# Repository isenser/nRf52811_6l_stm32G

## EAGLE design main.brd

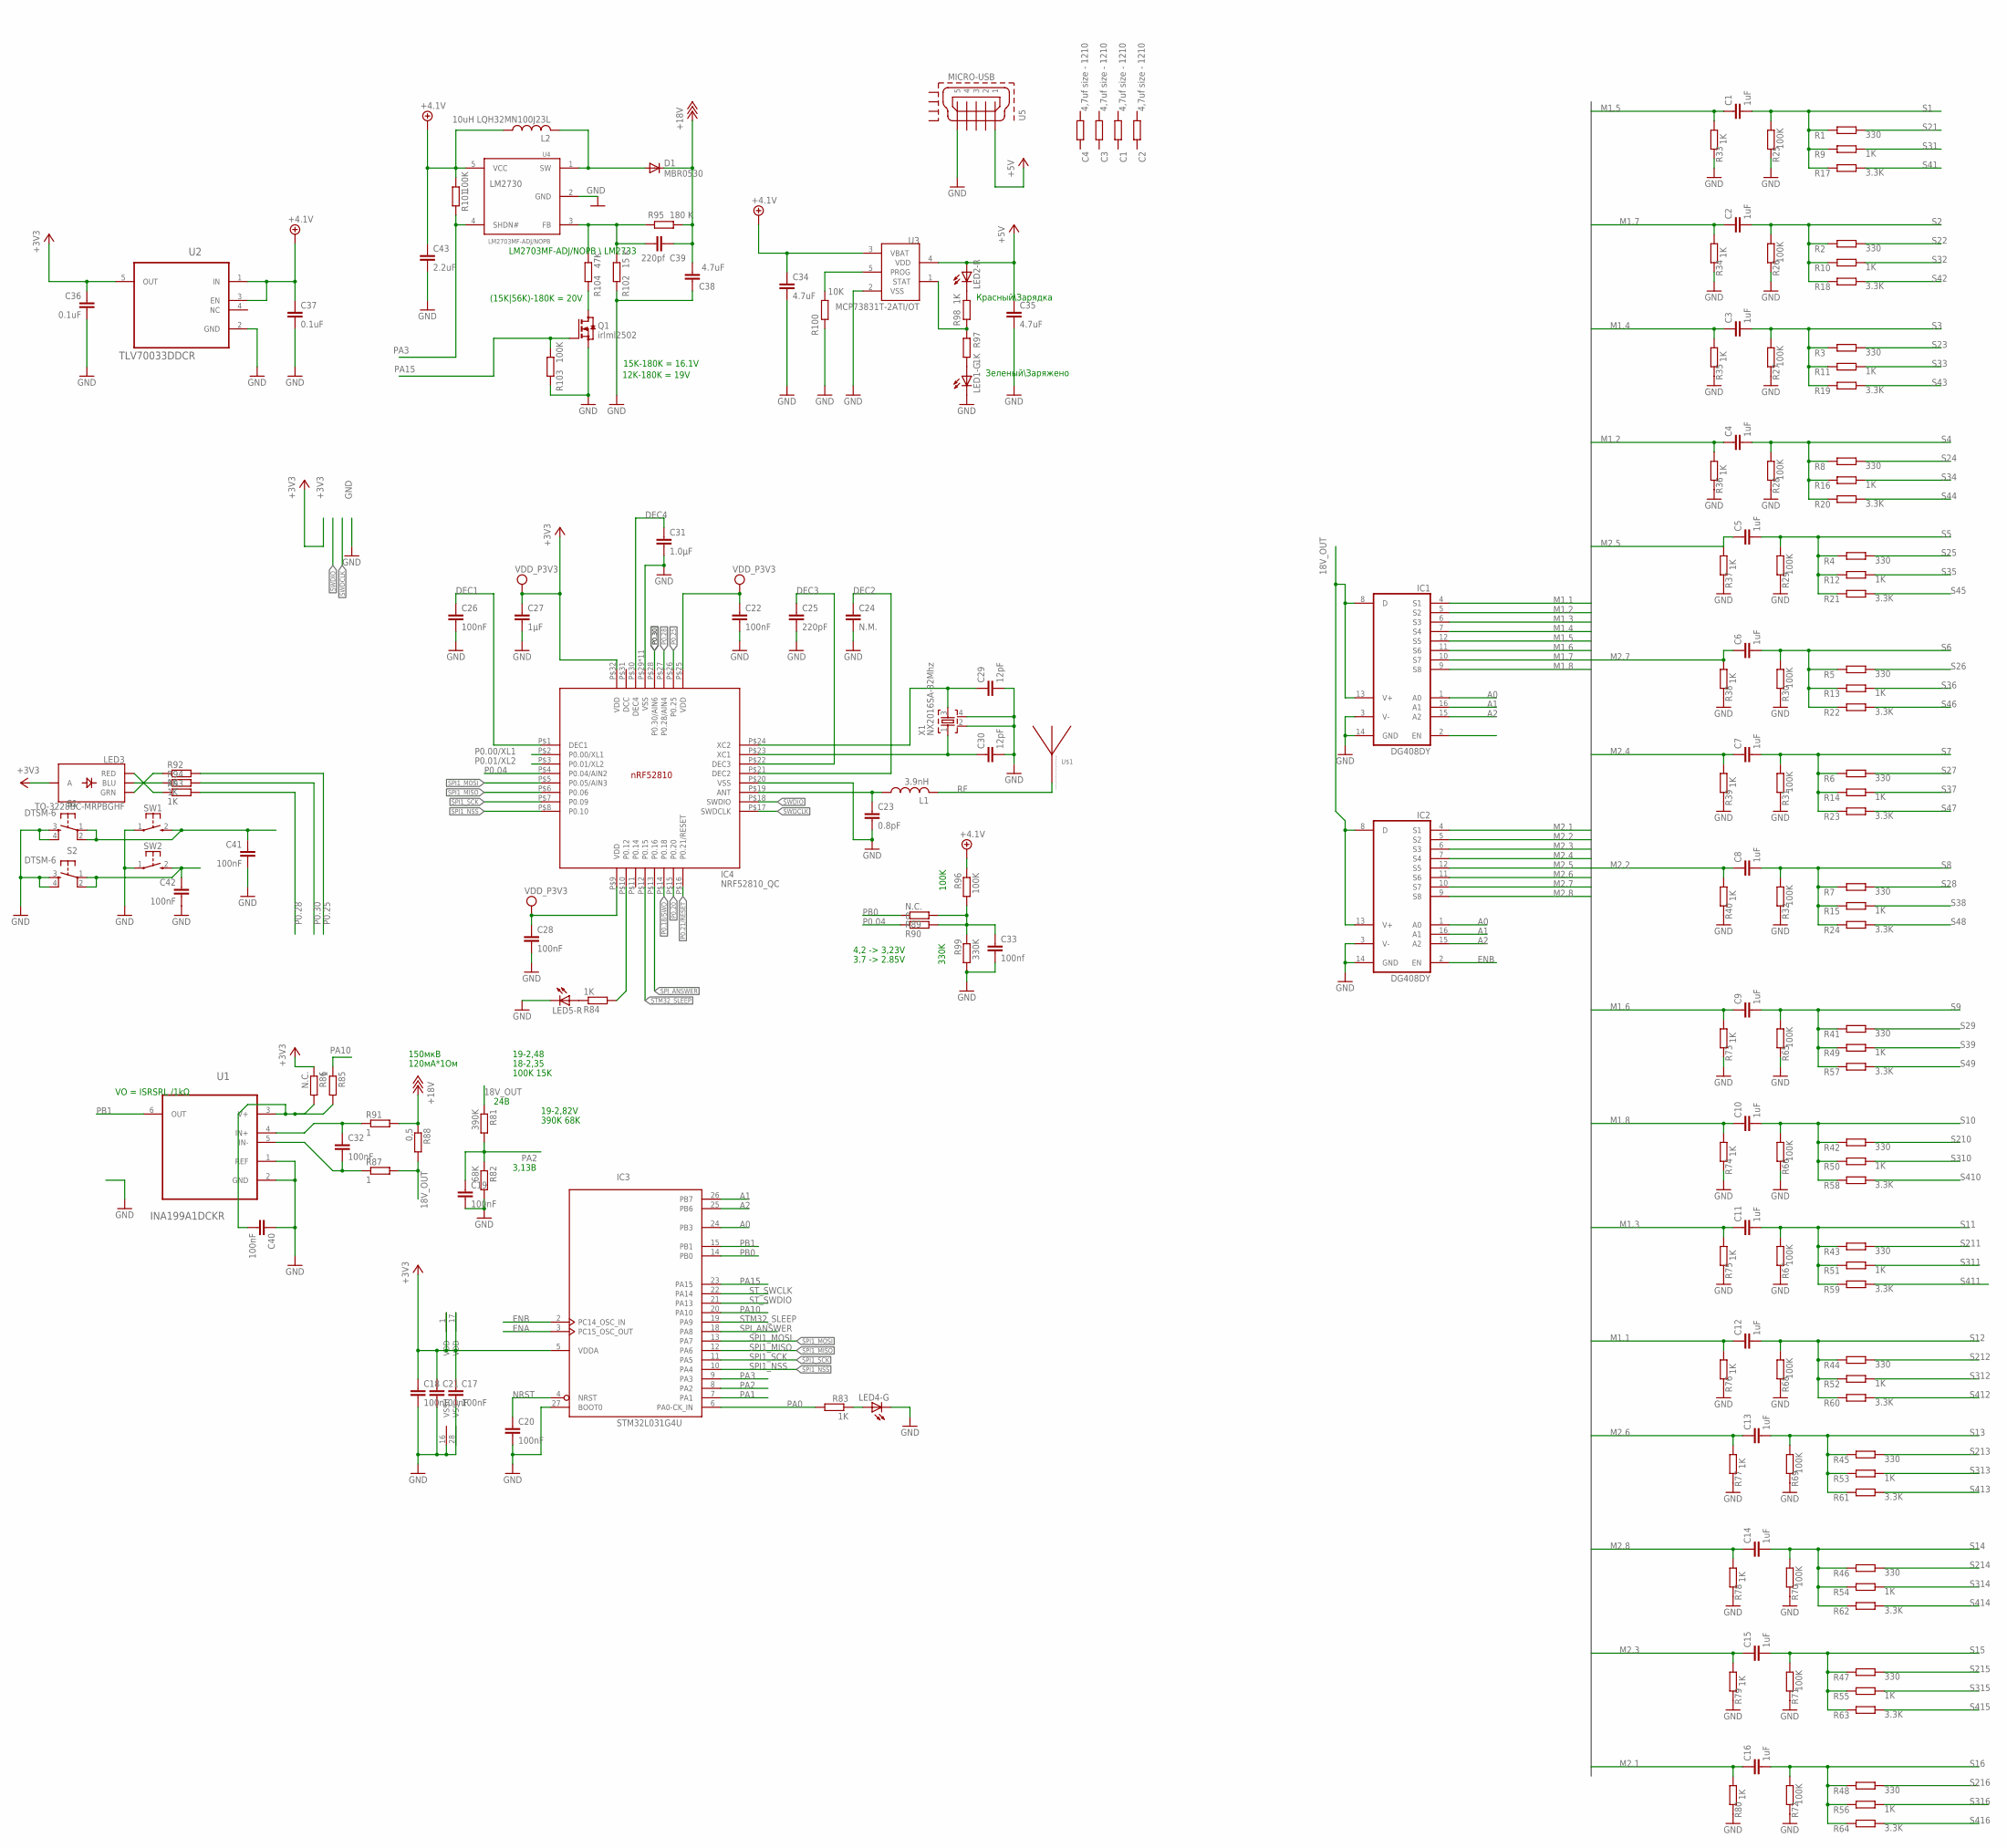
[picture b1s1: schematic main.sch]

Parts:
C1, C2, C3, C4, C5, C6, C7, C8, C9, C10, C11, C12, C13, C14, C15, C16: 1uF; C0402
C17, C18, C19, C20, C21, C22, C26, C28, C32, C40, C41, C42: 100nF; RESC0402_N
C23: 0.8pF; RESC0402_N
C24: N.M.; RESC0402_N
C25: 220pF; RESC0402_N
C27: 1µF; RESC0603_N
C29, C30: 12pF; RESC0402_N
C31: 1.0µF; RESC0402_M
C33: 100nf; RESC0402_N
C34, C35, C38: 4.7uF; C0805K
C36, C37: 0.1uF; C0402
C39: 220pf; C0603K
C43: 2.2uF; C0805K
D1: MBR0530; SOD123
IC1, IC2: DG408DY; SO16
IC3: STM32L031G4U; UFQFPN28
IC4: NRF52810_QC; QFN50P500X500X90-32_N
L1: 3.9nH; RESC0402_N
L2: 10uH LQH32MN100J23L; L2825P
LED1-G, LED2-R: LEDCHIP-LED0603; CHIP-LED0603
LED3: TO-3228BC-MRPBGHF; LED-TRICOLOR-SMD
LED4-G, LED5-R: LEDCHIPLED_0603; CHIPLED_0603
Q1: irlml2502; SOT23
R1, R2, R3, R4, R5, R6, R7, R8, R41, R42, R43, R44, R45, R46, R47, R48: 330; R0402
R9, R10, R11, R12, R13, R14, R15, R16, R33, R34, R35, R36, R37, R38, R39, R40, R49, R50, R51, R52, R53, R54, R55, R56, R73, R74, R75, R76, R77, R78, R79, R80, R92, R93, R94: 1K; R0402
R17, R18, R19, R20, R21, R22, R23, R24, R57, R58, R59, R60, R61, R62, R63, R64: 3.3K; R0402
R25, R26, R27, R28, R29, R30, R31, R32, R65, R66, R67, R68, R69, R70, R71, R72, R96, R101: 100K; R0402
R81: 390K; R0402
R82: 68K; R0402
R83, R84, R97, R98: 1K; R0603
R85, R87, R91: 1; R0402
R86, R89: N.C.; R0402
R88: 0,5; R0603
R90: 0; R0402
R95: 180 K; R0603
R99: 330K; R0402
R100: 10K; R0402
R102: 15 K; R0603
R103: 100K; R0603
R104: 47K; R0603
S1, S2: DTSM-6
SW1, SW2: KSS-2EG4430
U1: INA199A1DCKR; SOT65P210X110-6N
U2: TLV70033DDCR; SOT95P280X110-5N
U3: MCP73831T-2ATI/OT; SOT23-5L
U4: LM2703MF-ADJ/NOPB; SOT23-5
U5: MICRO-USB; 47589-0001
U$1: ANTENNA_QUARTER-WAVE_MONOPOLE_MEANDERED_LEFT; QWMP_MEANDERED_LEFT_+6
X1: NX2016SA-32Mhz; BT-XTAL_2016_N
С1, С2, С3, С4: 4,7uf size - 1210; R1206

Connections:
18V_OUT: IC1.8 (D), IC1.13 (V+), IC2.8 (D), IC2.13 (V+), R81.1, R87.2, R88.2
+3V3: C17.1, C18.1, C21.1, C22.1, C27.1, C28.1, C36.1, IC3.1 (VDD), IC3.5 (VDDA), IC3.17 (VDD), IC4.P$9 (VDD), IC4.P$25 (VDD), IC4.P$32 (VDD), LED3.A, R86.1, U2.5 (OUT)
+4.1V: C34.1, C37.1, C43.1, L2.1, R96.1, R101.1, U2.1 (IN), U2.3 (EN), U3.3 (VBAT), U4.5 (VCC)
+5V: C35.1, LED2-R.A, U3.4 (VDD), U5.1
+18V: C38.2, C39.1, D1.C, R88.1, R91.2, R95.1
A0: IC1.1 (A0), IC2.1 (A0), IC3.24 (PB3)
A1: IC1.16 (A1), IC2.16 (A1), IC3.26 (PB7)
A2: IC1.15 (A2), IC2.15 (A2), IC3.25 (PB6)
ANT1: C23.1, IC4.P$19 (ANT), L1.1
DEC1: C26.1, IC4.P$1 (DEC1)
DEC2: C24.1, IC4.P$21 (DEC2)
DEC3: C25.1, IC4.P$22 (DEC3)
DEC4: C31.1, IC4.P$30 (DEC4)
ENA: IC1.2 (EN), IC3.3 (PC15_OSC_OUT)
ENB: IC2.2 (EN), IC3.2 (PC14_OSC_IN)
GND: C17.2, C18.2, C19.2, C20.2, C21.2, C22.2, C23.2, C24.2, C25.2, C26.2, C27.2, C28.2, C29.2, C30.2, C31.2, C33.2, C34.2, C35.2, C36.2, C37.2, C38.1, C40.1, C41.2, C42.2, C43.2, IC1.3 (V-), IC1.14 (GND), IC2.3 (V-), IC2.14 (GND), IC3.16 (VSS), IC3.27 (BOOT0), IC3.28 (VSS), IC4.P$20 (VSS), IC4.P$29 (VSS), IC4.P$33 (VSS), IC4.P$34 (VSS), IC4.P$35 (VSS), IC4.P$36 (VSS), IC4.P$37 (VSS), IC4.P$38 (VSS), IC4.P$39 (VSS), IC4.P$40 (VSS), IC4.P$41 (VSS), IC4.P$42 (VSS), LED1-G.C, LED4-G.C, LED5-R.C, Q1.2 (S), R25.1, R26.1, R27.1, R28.1, R29.1, R30.1, R31.1, R32.1, R33.1, R34.1, R35.1, R36.1, R37.1, R38.1, R39.1, R40.1, R65.1, R66.1, R67.1, R68.1, R69.1, R70.1, R71.1, R72.1, R73.1, R74.1, R75.1, R76.1, R77.1, R78.1, R79.1, R80.1, R82.2, R99.2, R100.2, R102.2, R103.2, S1.3, S1.4, S2.3, S2.4, SW1.1, SW2.1, U1.1 (REF), U1.2 (GND), U2.2 (GND), U3.2 (VSS), U4.2 (GND), U5.5, X1.2, X1.4
M1.1: C12.1, IC1.4 (S1), R76.2
M1.2: C4.1, IC1.5 (S2), R36.2
M1.3: C11.1, IC1.6 (S3), R75.2
M1.4: C3.1, IC1.7 (S4), R35.2
M1.5: C1.1, IC1.12 (S5), R33.2
M1.6: C9.1, IC1.11 (S6), R73.2
M1.7: C2.1, IC1.10 (S7), R34.2
M1.8: C10.1, IC1.9 (S8), R74.2
M2.1: C16.1, IC2.4 (S1), R80.2
M2.2: C8.1, IC2.5 (S2), R40.2
M2.3: C15.1, IC2.6 (S3), R79.2
M2.4: C7.1, IC2.7 (S4), R39.2
M2.5: C5.1, IC2.12 (S5), R37.2
M2.6: C13.1, IC2.11 (S6), R77.2
M2.7: C6.1, IC2.10 (S7), R38.2
M2.8: C14.1, IC2.9 (S8), R78.2
unnamed: LED5-R.A, R84.1
unnamed: C29.1, IC4.P$24 (XC2), X1.3
unnamed: LED3.R (RED), R93.1
unnamed: C39.2, R95.2, R102.1, R104.1, U4.3 (FB)
unnamed: C32.2, R87.1, U1.5 (IN-)
unnamed: LED4-G.A, R83.1
unnamed: C32.1, R91.1, U1.4 (IN+)
unnamed: D1.A, L2.2, U4.1 (SW)
unnamed: C33.1, R89.2, R90.2, R96.2, R99.1
unnamed: LED3.G (GRN), R92.1
unnamed: LED1-G.A, R97.1
unnamed: Q1.3 (D), R104.2
unnamed: LED3.B (BLU), R94.1
unnamed: C40.2, R85.2, R86.2, U1.3 (V+)
unnamed: R97.2, R98.2, U3.1 (STAT)
unnamed: R100.1, U3.5 (PROG)
unnamed: LED2-R.C, R98.1
NRST: C20.1, IC3.4 (NRST)
P0.00/XL1: C41.1, IC4.P$2 (P0.00/XL1), S1.1, S1.2, SW1.2 (S)
P0.01/XL2: C42.1, IC4.P$3 (P0.01/XL2), S2.1, S2.2, SW2.2 (S)
P0.04: IC4.P$4 (P0.04/AIN2), R90.1
P0.12: IC4.P$10 (P0.12), R84.2
P0.18/SWO: IC4.P$14 (P0.18)
P0.20: IC4.P$15 (P0.20)
P0.21/RESET: IC4.P$16 (P0.21/RESET)
P0.25: IC4.P$26 (P0.25), R92.2
P0.28: IC4.P$27 (P0.28/AIN4), R93.2
P0.30: IC4.P$28 (P0.30/AIN6), R94.2
PA0: IC3.6 (PA0-CK_IN), R83.2
PA1: IC3.7 (PA1)
PA2: C19.1, IC3.8 (PA2), R81.2, R82.1
PA3: IC3.9 (PA3), R101.2, U4.4 (SHDN#)
PA10: IC3.20 (PA10), R85.1
PA15: IC3.23 (PA15), Q1.1 (G), R103.1
PB0: IC3.14 (PB0), R89.1
PB1: IC3.15 (PB1), U1.6 (OUT)
RF: L1.2, U$1.P$1
S1: C1.2, R1.1, R9.1, R17.1, R25.2
S2: C2.2, R2.1, R10.1, R18.1, R26.2
S3: C3.2, R3.1, R11.1, R19.1, R27.2
S4: C4.2, R8.1, R16.1, R20.1, R28.2
S5: C5.2, R4.1, R12.1, R21.1, R29.2
S6: C6.2, R5.1, R13.1, R22.1, R30.2
S7: C7.2, R6.1, R14.1, R23.1, R31.2
S8: C8.2, R7.1, R15.1, R24.1, R32.2
S9: C9.2, R41.1, R49.1, R57.1, R65.2
S10: C10.2, R42.1, R50.1, R58.1, R66.2
S11: C11.2, R43.1, R51.1, R59.1, R67.2
S12: C12.2, R44.1, R52.1, R60.1, R68.2
S13: C13.2, R45.1, R53.1, R61.1, R69.2
S14: C14.2, R46.1, R54.1, R62.1, R70.2
S15: C15.2, R47.1, R55.1, R63.1, R71.2
S16: C16.2, R48.1, R56.1, R64.1, R72.2
S21: R1.2
S22: R2.2
S23: R3.2
S24: R8.2
S25: R4.2
S26: R5.2
S27: R6.2
S28: R7.2
S29: R41.2
S31: R9.2
S32: R10.2
S33: R11.2
S34: R16.2
S35: R12.2
S36: R13.2
S37: R14.2
S38: R15.2
S39: R49.2
S41: R17.2
S42: R18.2
S43: R19.2
S44: R20.2
S45: R21.2
S46: R22.2
S47: R23.2
S48: R24.2
S49: R57.2
S210: R42.2
S211: R43.2
S212: R44.2
S213: R45.2
S214: R46.2
S215: R47.2
S216: R48.2
S310: R50.2
S311: R51.2
S312: R52.2
S313: R53.2
S314: R54.2
S315: R55.2
S316: R56.2
S410: R58.2
S411: R59.2
S412: R60.2
S413: R61.2
S414: R62.2
S415: R63.2
S416: R64.2
SPI1_MISO: IC3.12 (PA6), IC4.P$6 (P0.06)
SPI1_MOSI: IC3.13 (PA7), IC4.P$5 (P0.05/AIN3)
SPI1_NSS: IC3.10 (PA4), IC4.P$8 (P0.10)
SPI1_SCK: IC3.11 (PA5), IC4.P$7 (P0.09)
SPI_ANSWER: IC3.18 (PA8), IC4.P$13 (P0.16)
STM32_SLEEP: IC3.19 (PA9), IC4.P$12 (P0.15)
ST_SWCLK: IC3.22 (PA14)
ST_SWDIO: IC3.21 (PA13)
SWDCLK: IC4.P$17 (SWDCLK)
SWDIO: IC4.P$18 (SWDIO)
X2: C30.1, IC4.P$23 (XC1), X1.1

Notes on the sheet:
VO = ISRSRL /1kΩ
150мкВ
120мА*1Ом
24В
3,13В
18-2,35
19-2,48
4,2 -> 3,23V
3.7 -> 2.85V
15K-180K = 16.1V
12K-180K = 19V
(15K|56K)-180K = 20V
100K
330K
19-2,82V
390K 68K
100K 15K
Красный\Зарядка
Зеленый\Заряжено
LM2703MF-ADJ/NOPB \ LM2733

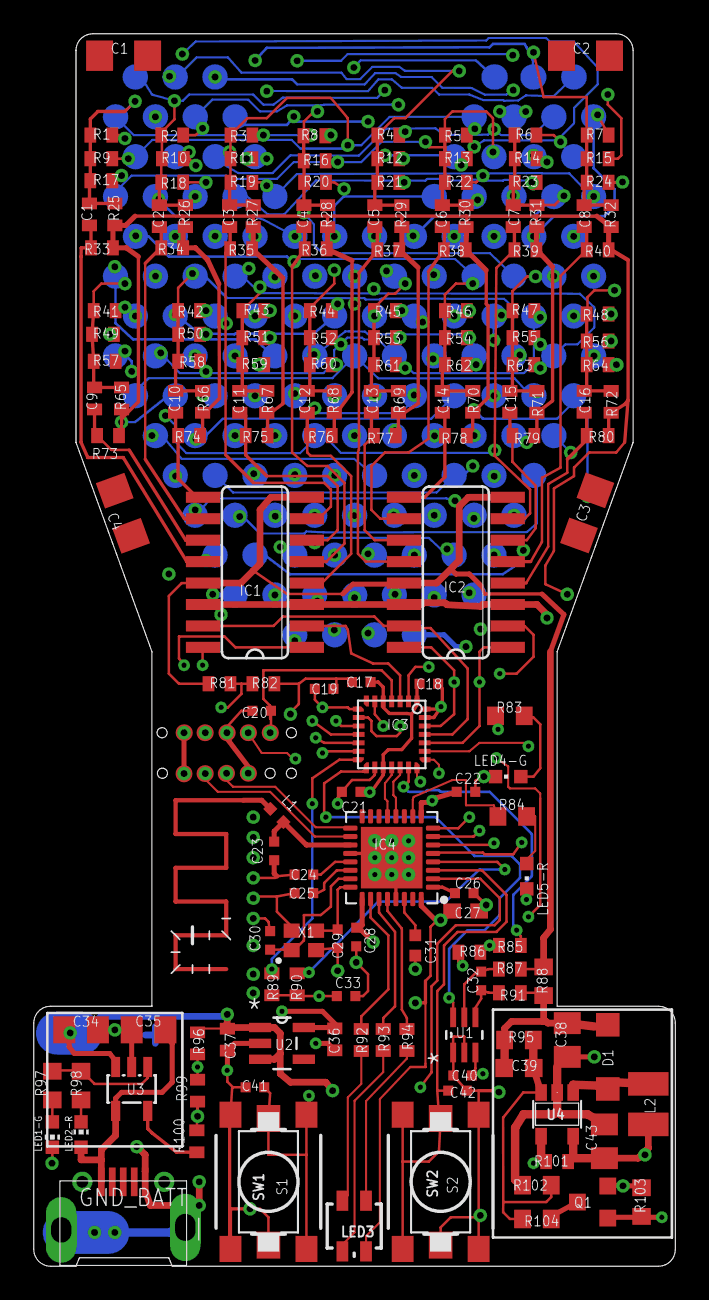
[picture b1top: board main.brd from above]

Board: 6 copper layers, 38.0 x 73.0 mm, 175 parts (0 on the bottom side), 88 nets.

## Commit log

2022-08-19 v1
    v1

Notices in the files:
parts and their libraries:
vreg-pulse: 2009 Draw by Ivan A-R. License CC-BY-SA 3.0
SparkFun-LED: Licensing: Creative Commons ShareAlike 4.0 International - https://creativecommons.org/licenses/by-sa/4.0
con-molex-usb: (C) 2014 Tomasz Boleslaw CEDRO, cederom@tlen.pl, http://www.tomek.cedro.info.
